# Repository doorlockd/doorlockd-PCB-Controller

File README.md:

# Doorlockd controller
This repository contains a PCB for a doorlockd controller, which
(together with a remote card reader) reads RFID tags and controls a lock
solenoid or other devices.

The main controller can be a Rock Pi S or Milk-V Duo S Linux board, which is
stacked on top of this PCB. This PCB then provides power, a bunch of I/O
options (for buttons, leds, RFID reader, solenoids, etc.) plus a bit of
stripboard for custom additions.

This PCB is designed to be used with other [doorlockd hardware and
software](https://github.com/doorlockd/), but can also be used with any
other software running on the same Linux boards.

See the [doorlockd organization page](https://github.com/doorlockd/) for
some info about the system in practice.

## Features

This PCB provides:

 - Support for a Rock Pi S or Milk-V Duo board. To support both, in
   addition to software chagnes, some jumpers must be set correctly, and
   on there are some differences between both board for the pins on the
   stripboard area.
 - 6.5-36VDC power input (VIN), regulated to 5V to power the Linux board. 3V3
   then taken from the Linux board.
 - 4 Generic I/O circuits (numbered IO1-IO4), can be configured (by
   soldering) as direct input/output, output with series resistance or
   input with RC filter.  Available on 2.54mm pin headers directly, or
   up to 5 pins on screw terminals via wire bridges.
 - 2 low-side switched FET outputs (numbered OUT5 and OUT6) for solenoid
   or other high-current loads on screw terminals (high-side pin
   selectable between 5V and VIN).
 - UART connection to the RFID reader (e.g.
   [doorlockd-PCB-Reader](/doorlockd/doorlockd-PCB-Reader)), available
   on a square (2x2) or rectangular (1x4) connector with standard 2.54mm
   pitch. The square connector makes it easy to feed the cable through
   a round hole in e.g. a door frame.
 - 4-pin 2.54mm connector for UART connection to . Available as 1x4 pin, or
   2x2 pin (for easier feeding through a circular hole).
 - Audio (line out) on 3.5mm jack or pin header (direct from Linux
   board).
 - Stripboard area for custom extra peripherals.

## Pinout
Because the board supports two different linux board, the actual pinout
differs based on the board used.

The pins near the stripboard are intended for future experiments. The
pins to the right of the stripboard are either generic GPIO pins, or
dedicated function (SPI and I²C) pins that have the same function both
boards. All these pins support 3.3V (except for P26, which an 1.8V ADC
pin on the Rock Pi).

The pins below the stripboard are divided into a separate header for
each of the boards, since what is an IO pin on one board could be a GND
or some other special-function pin on the other. The Milk-V pins below
the stripboard only support up to 1.8V (see below).

The spreadsheet in this repository gives an overview of all pins
available on the board, where they are connected on both types of
board and what pin functions are available on those pins.

In the spreadsheet, the "doorlockd-PCB-Controller" is the main sheet to
use. This lists all the pins on the controller PCB, along with the pin
on U2 (Rock pi S or Milk-V Duo S) that it is connected to. To the right
there are two sections, one for each board, showing the name that the
board gives to that pin, and the available pin functions.

For the pin functions, three columns are available. The first column
shows a filter expression, such as `*GPIO*` and the second column shows
all pin functions (on that pin) that match the filter. The third column
is similar, except that the filter is taken from the column header (so
you can filter all pins at the same time to find a particular pin
function). You can use the `*` filter to list all available pin
functions.

The other sheets in the spreadsheet file provide are similar, but
start from the pins on the Milk-V and Rock Pi boards, instead of the
doorlockd controller PCB.

### Board selection jumpers
Some fixed-function pins (audio and card reader UART) are not (all)
available on the same place on both boards. For this reason jumpers JP4
and JP5 must be configured for the board used. If the jumpers are wrong,
the card reader RX and TX will be swapped, and the audio left channel
will be connected to 5V or a mic input channel.

### 3.3V and 1.8V pins
On the Rock Pi S all pins (except ADC) operate at 3.3V, but the Milk-V
Duo S has both 3.3V and 1.8V pins, so care should be taken when using
those pins. These 1.8V pins are used on the high-current FET inputs
(where they are shielded from the outside worled) and available on the
stripboard (on J18), where care should be taken to not overload them.

If a Milk-V Duo is used and the 3.3V pins on J22 are not sufficient, the
1.8V pins on J18 can be used. If 3.3V operation is needed, the board is
designed so a standard level shifter board can be connected with the low
side plugging into J18 and the high side into stripboard pins.

For example, using [this 8-channel shifter from
Adafruit](https://www.adafruit.com/product/395), using J18-1 (P29) as
VCCA and J18-10 (P27) as OE (configuring P29 as output high and P27 as
output low). Pin P43 is available nearby to be used for VCCB. Similarly,
[this 4-channel shfiter](https://www.adafruit.com/product/1875) can also
be used.

### ADC pins
On both boards, once ADC pin is available.

Rock pi has P26, located to the right of the stripboard. This pin is not
usable as a GPIO.

Milk-V has P46, located below the stripboard. This pin can also be used
as a GPIO.

On both boards, the ADC pins support up to 1.8V only.

## Housing
PCB dimensions: 132×103mm

The PCB has oval mounting holes supporting two different housing series:

 - RND455 121×171mm, with mounting holes spaced 118×91mm.
   This series includes: RND 455-01088 (dark grey ABS, IP67), RND
   455-01072 (light grey polycarbonate with clear lid, IP67), RND
   455-00242 (light grey polycarbonate with clear lid, IP65), 

 - RP1235 165×125mm, with mounting holes spaced 120×90mm.
   This series includes: RP1235BF (light grey ABS), RP1235BFC (light
   grey ABS with clear lid), RP1230BF (light grey polycarbonate),
   RP1230BFC (light grey polycarbonate with clear lid). Also
   RP1235/RP1235C/RP1230/RP1230C are the same but without the bottom
   flange for wall mounting. All are IP65.

The RND series is a lot cheapter, but not as widely available as the
Hammond ones.

## Origins & grid
The origins in the PCB layout became a bit inconsistent. The aux/drill
origin is set to the top left corner of the PCB (so you can set the
KiCad Display origin to drill in the KiCad preferences to get
board-local coordinates).

The grid origin was originally intended to be in the center of the
board, but with some board resizing it got misplaced. To not mess up
existing grid-aligned objects, it was left in place.

The idea was to put all connectors on a 100mil grid (to allow adding
another bit of stripboard on top and connect it to the connectors if
needed), and then components on a 20mil grid, but this was not
consistently done (so different parts of the PCB are unaligned with each
other. Oh well.

## License
Copyright 2025 Diederik Hamelink (wie-niet)
Copyright 2025 Matthijs Kooijman (matthijs@stdin.nl)

This source describes Open Hardware and is licensed under the CERN-OHL-P
v2 or any later version.

You may redistribute and modify this documentation and make products
using it under the terms of the CERN-OHL-P v2 (https:/cern.ch/cern-ohl).

This documentation is distributed WITHOUT ANY EXPRESS OR IMPLIED
WARRANTY, INCLUDING OF MERCHANTABILITY, SATISFACTORY QUALITY AND FITNESS
FOR A PARTICULAR PURPOSE. Please see the CERN-OHL-P v2 for applicable
conditions

See LICENSE.txt for the full license text.

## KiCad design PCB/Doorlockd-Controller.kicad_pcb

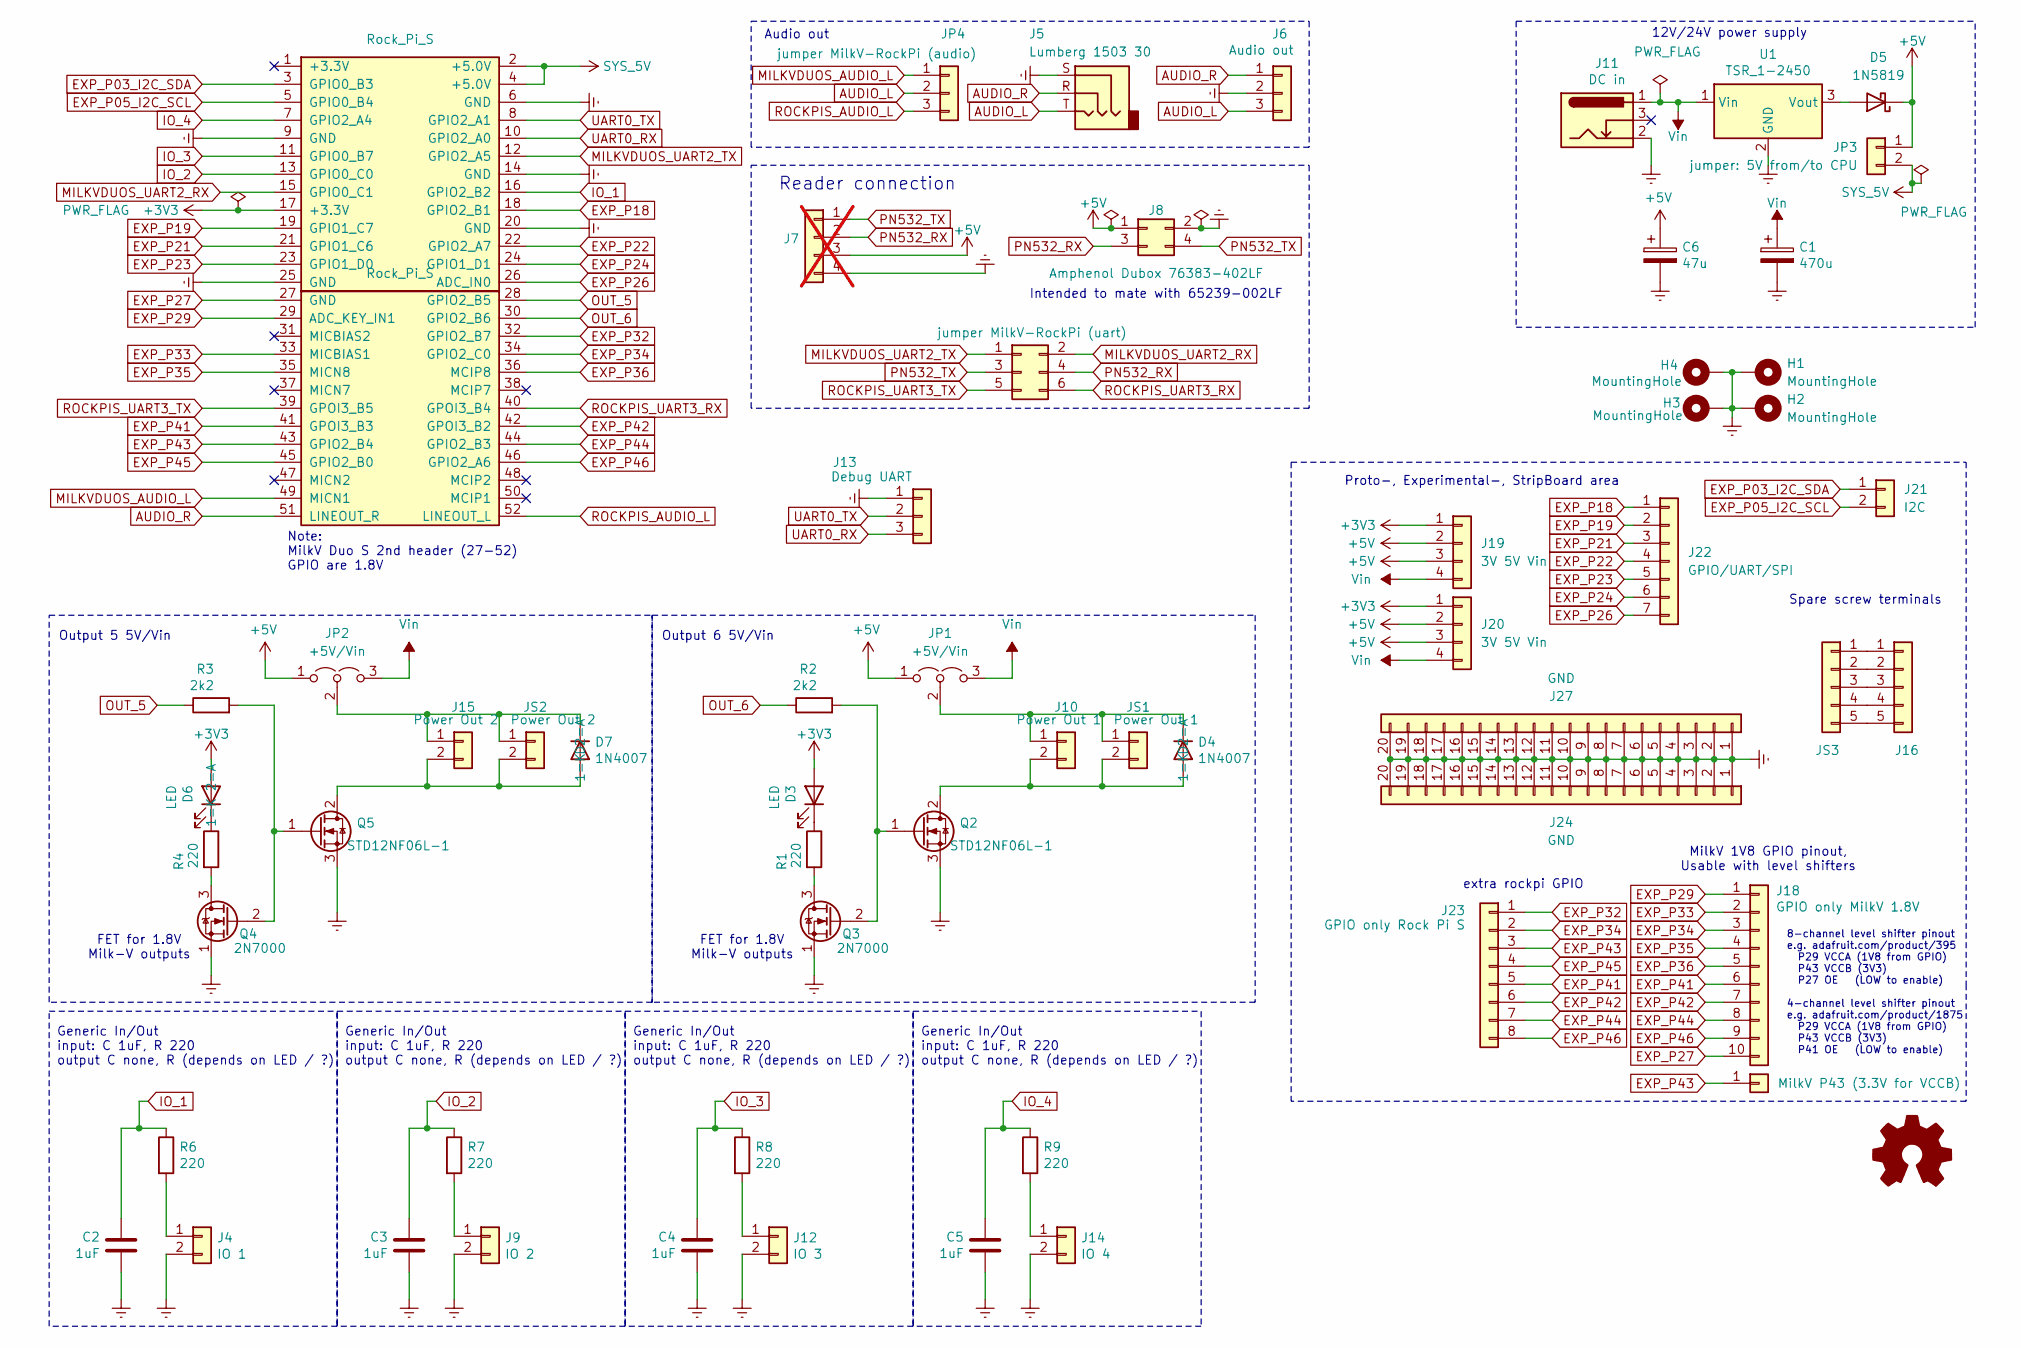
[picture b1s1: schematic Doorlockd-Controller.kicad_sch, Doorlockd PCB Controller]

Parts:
C1: 470u; CP_Radial_D10.0mm_P5.00mm
C2, C3, C4, C5: 1uF; C_Disc_D7.5mm_W4.4mm_P5.00mm
C6: 47u; CP_Radial_D10.0mm_P5.00mm
D3, D6: LED; LED_D5.0mm
D4, D7: 1N4007; D_DO-41_SOD81_P7.62mm_Horizontal
D5: 1N5819; D_DO-41_SOD81_P10.16mm_Horizontal
H1, H2, H3, H4: MountingHole; MountingHole_Dual_3.2mm_M3_Offset1x0.5mm
J1: MilkV P43 (3.3V for VCCB); StripBoard_1x01_P2.54mm
J4: IO 1; Molex_KK-254_AE-6410-02A_1x02_P2.54mm_Vertical
J5: Lumberg 1503 30; Jack_3.5mm_Lumberg_1503_07_Horizontal
J6: Audio out; Molex_KK-254_AE-6410-03A_1x03_P2.54mm_Vertical
J7: Conn_01x04; PinHeader_1x04_P2.54mm_Vertical; not fitted
J8: Amphenol Dubox ‎76383-402LF‎; PinHeader_2x02_P2.54mm_Horizontal
J9: IO 2; Molex_KK-254_AE-6410-02A_1x02_P2.54mm_Vertical
J10: Power Out 1; Molex_KK-254_AE-6410-02A_1x02_P2.54mm_Vertical
J11: DC in; BarrelJack_Horizontal
J12: IO 3; Molex_KK-254_AE-6410-02A_1x02_P2.54mm_Vertical
J13: Debug UART; PinHeader_1x03_P2.54mm_Vertical
J14: IO 4; Molex_KK-254_AE-6410-02A_1x02_P2.54mm_Vertical
J15: Power Out 2; Molex_KK-254_AE-6410-02A_1x02_P2.54mm_Vertical
J16: to extra screw conn.; StripBoard_1x05_P2.54mm
J18: GPIO only MilkV 1.8V; StripBoard_1x10_P2.54mm
J19, J20: 3V 5V Vin; StripBoard_1x04_P2.54mm
J21: I2C; StripBoard_1x02_P2.54mm
J22: GPIO/UART/SPI; StripBoard_1x07_P2.54mm
J23: GPIO only Rock Pi S; StripBoard_1x08_P2.54mm
J24, J27: GND; StripBoard_1x20_P2.54mm_Square
JP1, JP2: +5V/Vin; PinHeader_1x03_P2.54mm_Vertical
JP3: jumper: 5V from/to CPU; PinHeader_2x01_P2.54mm_Vertical
JP4: jumper MilkV-RockPi (audio); PinHeader_1x03_P2.54mm_Vertical
JP5: jumper MilkV-RockPi (uart); PinHeader_2x03_P2.54mm_Vertical
JS1: Power Out 1; TerminalBlock_Phoenix_MKDS-3-2-5.08_1x02_P5.08mm_Horizontal
JS2: Power Out 2; TerminalBlock_Phoenix_MKDS-3-2-5.08_1x02_P5.08mm_Horizontal
JS3: Extra Screw conn; TerminalBlock_Phoenix_MKDS-3-5-5.08_1x05_P5.08mm_Horizontal
Q2, Q5: STD12NF06L-1; TO-251-3_Vertical
Q3, Q4: 2N7000; TO-92_Wide
R1, R4, R6, R7, R8, R9: 220; R_Axial_DIN0207_L6.3mm_D2.5mm_P10.16mm_Horizontal
R2, R3: 2k2; R_Axial_DIN0207_L6.3mm_D2.5mm_P10.16mm_Horizontal
U1: TSR_1-2450; Converter_DCDC_TRACO_TSR-1_THT
U2: Rock_Pi_S

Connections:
+3V3: D3.2 (A), D6.2 (A), J19.1, J20.1, U2.17 (+3.3V)
+5V: C6.1, D5.1 (K), J7.3, J8.1, J19.2, J19.3, J20.2, J20.3, JP1.1 (A), JP2.1 (A), JP3.1
AUDIO_L: J5.T, J6.3, JP4.2
AUDIO_R: J5.R, J6.1, U2.51 (LINEOUT_R)
EXP_P03_I2C_SDA: J21.1, U2.3 (GPIO0_B3)
EXP_P05_I2C_SCL: J21.2, U2.5 (GPIO0_B4)
EXP_P18: J22.1, U2.18 (GPIO2_B1)
EXP_P19: J22.2, U2.19 (GPIO1_C7)
EXP_P21: J22.3, U2.21 (GPIO1_C6)
EXP_P22: J22.4, U2.22 (GPIO2_A7)
EXP_P23: J22.5, U2.23 (GPIO1_D0)
EXP_P24: J22.6, U2.24 (GPIO1_D1)
EXP_P26: J22.7, U2.26 (ADC_IN0)
EXP_P27: J18.10, U2.27 (GND)
EXP_P29: J18.1, U2.29 (ADC_KEY_IN1)
EXP_P32: J23.1, U2.32 (GPIO2_B7)
EXP_P33: J18.2, U2.33 (MICBIAS1)
EXP_P34: J18.3, J23.2, U2.34 (GPIO2_C0)
EXP_P35: J18.4, U2.35 (MICN8)
EXP_P36: J18.5, U2.36 (MCIP8)
EXP_P41: J18.6, J23.5, U2.41 (GPOI3_B3)
EXP_P42: J18.7, J23.6, U2.42 (GPOI3_B2)
EXP_P43: J1.1, J23.3, U2.43 (GPIO2_B4)
EXP_P44: J18.8, J23.7, U2.44 (GPIO2_B3)
EXP_P45: J23.4, U2.45 (GPIO2_B0)
EXP_P46: J18.9, J23.8, U2.46 (GPIO2_A6)
Earth: C1.2, C2.1, C3.1, C4.1, C5.1, C6.2, H1.1, H2.1, H3.1, H4.1, J4.2, J5.S, J6.2, J7.4, J8.2, J9.2, J11.2, J12.2, J13.1, J14.2, J24.1, J24.2, J24.3, J24.4, J24.5, J24.6, J24.7, J24.8, J24.9, J24.10, J24.11, J24.12, J24.13, J24.14, J24.15, J24.16, J24.17, J24.18, J24.19, J24.20, J27.1, J27.2, J27.3, J27.4, J27.5, J27.6, J27.7, J27.8, J27.9, J27.10, J27.11, J27.12, J27.13, J27.14, J27.15, J27.16, J27.17, J27.18, J27.19, J27.20, Q2.3 (S), Q3.1 (S), Q4.1 (S), Q5.3 (S), U1.2 (GND), U2.6 (GND), U2.9 (GND), U2.14 (GND), U2.20 (GND), U2.25 (GND)
IO_1: C2.2, R6.1, U2.16 (GPIO2_B2)
IO_2: C3.2, R7.1, U2.13 (GPIO0_C0)
IO_3: C4.2, R8.1, U2.11 (GPIO0_B7)
IO_4: C5.2, R9.1, U2.7 (GPIO2_A4)
MILKVDUOS_AUDIO_L: JP4.1, U2.49 (MICN1)
MILKVDUOS_UART2_RX: JP5.2, U2.15 (GPIO0_C1)
MILKVDUOS_UART2_TX: JP5.1, U2.12 (GPIO2_A5)
unnamed: D3.1 (K), R1.1
unnamed: D4.2 (A), J10.2, JS1.2, Q2.2 (D)
unnamed: D4.1 (K), J10.1, JP1.2 (C), JS1.1
unnamed: D5.2 (A), U1.3 (Vout)
unnamed: D6.1 (K), R4.1
unnamed: D7.2 (A), J15.2, JS2.2, Q5.2 (D)
unnamed: D7.1 (K), J15.1, JP2.2 (C), JS2.1
unnamed: J4.1, R6.2
unnamed: J9.1, R7.2
unnamed: J12.1, R8.2
unnamed: J14.1, R9.2
unnamed: J16.1, JS3.1
unnamed: J16.2, JS3.2
unnamed: J16.3, JS3.3
unnamed: J16.4, JS3.4
unnamed: J16.5, JS3.5
unnamed: Q2.1 (G), Q3.2 (G), R2.2
unnamed: Q3.3 (D), R1.2
unnamed: Q4.3 (D), R4.2
unnamed: Q4.2 (G), Q5.1 (G), R3.2
OUT_5: R3.1, U2.28 (GPIO2_B5)
OUT_6: R2.1, U2.30 (GPIO2_B6)
PN532_RX: J7.2, J8.3, JP5.4
PN532_TX: J7.1, J8.4, JP5.3
ROCKPIS_AUDIO_L: JP4.3, U2.52 (LINEOUT_L)
ROCKPIS_UART3_RX: JP5.6, U2.40 (GPOI3_B4)
ROCKPIS_UART3_TX: JP5.5, U2.39 (GPOI3_B5)
SYS_5V: JP3.2, U2.2 (+5.0V), U2.4 (+5.0V)
UART0_RX: J13.3, U2.10 (GPIO2_A0)
UART0_TX: J13.2, U2.8 (GPIO2_A1)
Vin: C1.1, J11.1, J19.4, J20.4, JP1.3 (B), JP2.3 (B), U1.1 (Vin)

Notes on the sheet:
Generic In/Out input: C 1uF, R 220 output C none, R (depends on LED / ?)
Reader connection
Output 5 5V/Vin
FET for 1.8V Milk-V outputs
MilkV 1V8 GPIO pinout, Usable with level shifters
Intended to mate with 65239-002LF
Spare screw terminals
Output 6 5V/Vin
8-channel level shifter pinout e.g. adafruit.com/product/395 P29 VCCA (1V8 from GPIO) P43 VCCB (3V3) P27 OE (LOW to enable) 4-channel level shifter pinout e.g. adafruit.com/product/1875 P29 VCCA (1V8 from GPIO) P43 VCCB (3V3) P41 OE (LOW to enable)
Proto-, Experimental-, StripBoard area
extra rockpi GPIO
Audio out
Note: MilkV Duo S 2nd header (27-52) GPIO are 1.8V
12V/24V power supply

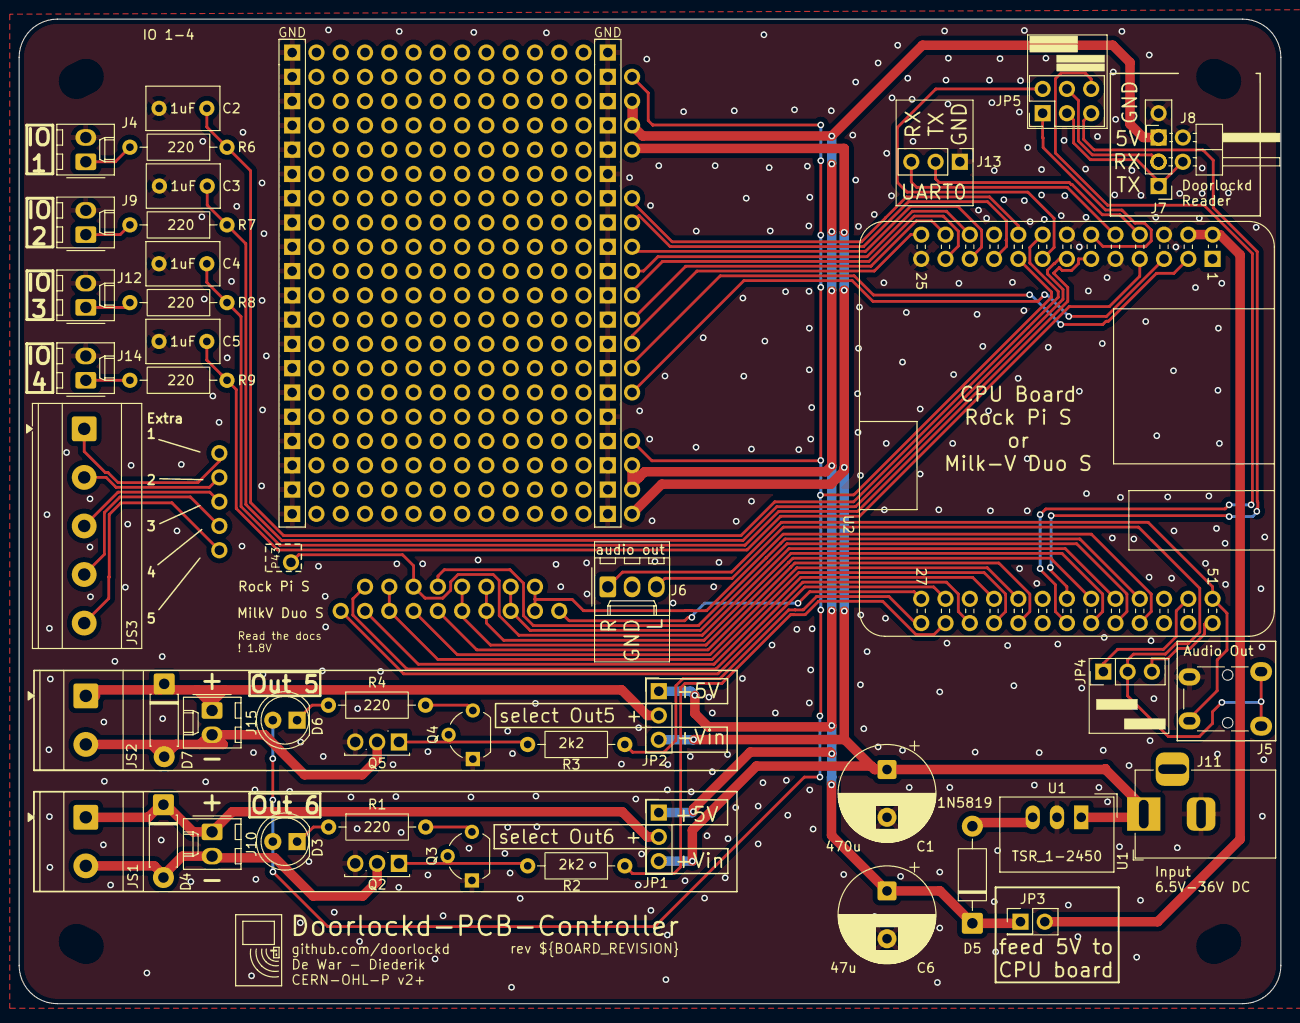
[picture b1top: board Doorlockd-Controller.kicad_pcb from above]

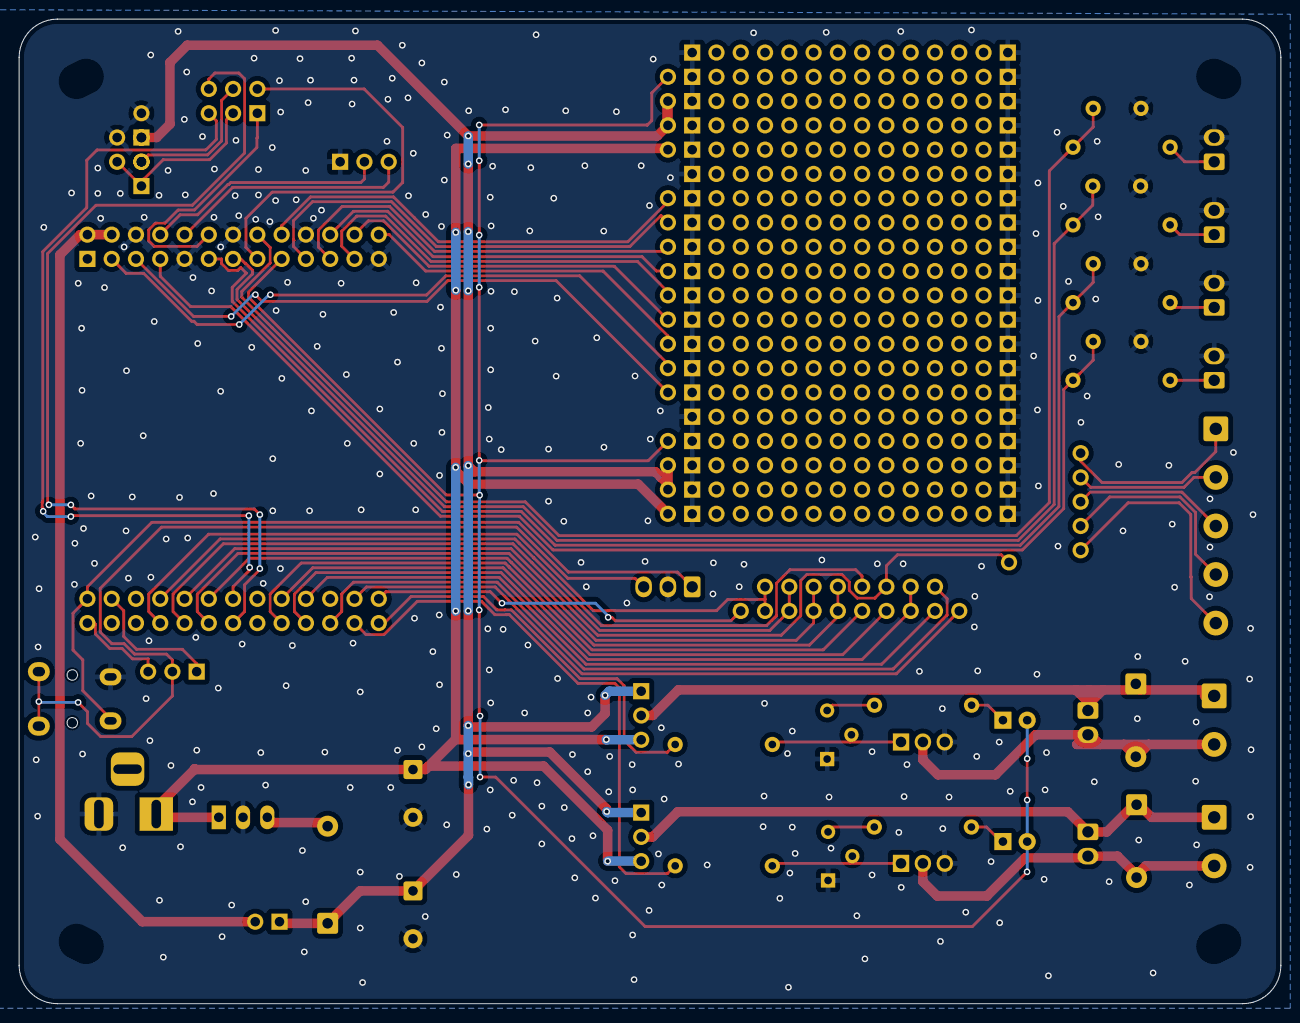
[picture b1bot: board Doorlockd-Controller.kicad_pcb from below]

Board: 2 copper layers, 132.0 x 103.0 mm, 59 parts (2 on the bottom side), 65 nets.

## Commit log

2025-06-17 Add initial version
2025-06-17 Added kibot workflow for automatic versioning
    see https://github.com/matthijskooijman/PCB-workflows
2025-06-17 Fixed various ERC rule errors and warnings
2025-06-17 Fixed earlier fixed problems overwritten by last attemp to fix problems
2025-06-17 Adds kibot schematics pdf
2025-06-17 Adds ground plate vias
2025-06-17 First version, release candidate for version 2.
2025-06-17 Beta realease v2.0b1
2025-06-18 Note audio jack actually to be used
    The 1503 07 for which we used a footprint is no longer available, but
    the 1503 30 should be pin compatible.
2025-06-18 Update footprints in schematic (from PCB)
2025-06-18 Mark stripboard as "not in schematic"
    This prevents deleting it when updating PCB from schematic.
2025-06-18 Update PCB from schematic
    This imports fields (description and datasheet) for some symbols that
    were previously somehow not included.
2025-06-18 Fixed correct pins for ROCKPIS_UART3_RX/TX connecting PN532 Reader
2025-06-18 Fixed Pin 15 and updated the spreadsheet MILKVDUOS_UART2_RX was connected to the wrong pin14 -> pin15
2025-06-18 Fixed Thermal relief connection to zone incomplete
    Pin 14 of Rock Pi S/MilkV Duo S by adding via to bottom layer
    Thermal relief connection to zone incomplete (layer F.Cu; 1 spokes connected to isolated island)
2025-06-23 Fixed readability silkscreen
2025-06-24 Fixed and improved spreadsheet, pcb and schema
    PCB and Schema:
    improved netlabels for PN532 related pins.
    improved netlabels for OUT_1 / OUT_2
    improved netlabels for EXP P03 / EXP P05 , and fixed copper lines accoording to silkscreen labels.
    added 3.3V pin on PCB intended for lelvel shifter Milk V DUO S (EXP_P43)
    Added help lines for mountingholes on fab layer.
2025-06-24 Fixes 3d-view for StripBoard 1x01
2025-06-24 Replace icon by cleaner SVG version
2025-06-26 Updated spreadsheets, adds StripBoard Extra Pins overview
2025-06-26 Cosmetic schematic changes
2025-06-26 Do not ignore orphan global labels in ERC
2025-06-26 Cosmetic PCB changes
2025-06-26 Adds overview tables of all available GPIO pins
2025-08-14 Revert "Adds kibot schematics pdf"
    This reverts commit 4520ee80d4823f830d35762883774dac6c1f55b6.
    The default config already generates a schematic, so no need for
    a custom config here.
2025-08-14 Improve mounting hole accuracy
    Turns out these holes were actually 26.565 degrees (atan(0.5)), not 22.5.
    This fixes the footprint to angle the pad at 26.5 and puts the courtyard
    and user comments figures in the exactly correct spot.
    This also renames the footprint, switching from specifying the angle
    (which would be inexact) to the center offset of the second hole.
2025-08-14 Replace STU60N3LH5 FET with STD12NF06L-1
    The former is not available anymore since a while, the latter is
    another IPAK FET with similar specs.
2025-08-14 Add PCB and mounting hole dimensions
    This also removes the text area with some of these dimensions and info
    about what housings are intended to be used. The latter will be readded
    in the README.
2025-08-24 Update PCB from schematic
    For some reason this changes all empty datasheets to ~.
2025-08-24 Refill zones and let KiCad update tables
    Somehow when opening this file in my KiCad version, it makes changes to
    table definitions in the file. Maybe this is a difference between my and
    Diederik's versions, or Linux and OSX, but well.
2025-08-24 Add README
2025-08-24 Change license to CERN-OHL-P v2+
    Also makes some other small tweaks to the title sheet.
2025-08-24 Set explicit permissions in workflow file
    This allows operation with repositories where the default permissions
    are read-only. By specifying explicit permissions, the workflow runs
    with raised permissions.
2025-08-24 Some silkscreen tweaks
2025-08-24 Change LED resistors to 220
    This reduces LED current a bit, and reduces BOM count.
2025-09-04 PCB-workflows: Update
    This includes the following commits:
    95c1b8c Remove echo accidentally added in the previous commit
    1c8f120 Fix compatibility on Linux again
    8a94424 Switch to blender for 3D rendering
    f3d7aa1 Add 3D render to github release body
    71275f1 Set explicit permissions in workflow file
2025-09-04 Use correct IPAK footprint
    This used the SIPAK footprint, but that is slightly different (and has
    no 3D model), so use the IPAK/TO-251-3 footprint instead.
2025-09-11 Improve note about audio connector
    Turns out the two mentioned connectors have the same footprint, but are
    not pin-compatible (ring and sleeve are swapped).
2025-09-11 Swap output 5 and 6
    The were accidentally mislabeled in the silkscreen. To preserve the
    logical order on the PCB, the silk is unchanged, but the schematic is
    changed to swap them instead.
2025-09-11 Use MOSI/MISO instead of SDO/SDI on silk
2025-09-11 Improve level shifter note in schematic
2025-09-11 Update README and pinout spreadsheet
2025-09-11 made title, boardname and silk consistent
2025-09-11 Add note about jumpers to README
2025-09-11 Move some vias away from silk
2025-09-11 Remove 3D models for stripboard headers
    These models were already hidden, but when a hidden model is present
    kibot still renders solder blobs in the pads. To work around that, just
    remove the models entirely.
2025-09-11 Fix a via position and do a zone fill
    This via was accidentally put on top of a trace, and when modifying the
    vias, a zone fill was forgotten.
2025-09-11 Remove COMPONENTS_DATE from silkscreen
    This date is intended to reflect the component selection, which can be
    changed independent of the PCB layout, so it should not be reflected on
    the actual board.
2025-09-11 Update and fix 3D render in README
2025-09-11 Improved logo and boardname position
2025-09-11 Release v2.0
2025-09-18 Add 3D models to Rock Pi footprint
    This just adds two pin socket models with an offset.
2025-09-18 Make mounting holes non-plated
    It seems that having a pad around an oval hole confuses Aisler and
    produces a weird result (at least in the preview, Aisler has not yet
    finished investigating whether there is also a problem in actual
    production).
    As a workaround, make the holes nonplated (and make the pad size equal
    to the hole size), since we do not really need the grounding currently
2025-09-18 Re-release v2.0
    Turns out the oval mounting holes caused an issue with Aisler, so they
    were changed to be non-plated to work around that. So this is the real
    2.0 version that will be manufactured.
2025-10-01 Swap output 5 and 6
    was already updated in kicad but not in the spreadsheet

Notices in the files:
PCB/Doorlockd-Controller.kicad_pcb:
Copyright 2025 Diederik Hamelink (wie-niet) & Matthijs Kooijman
Licensed under CERN-OHL-P v2 or any later version
